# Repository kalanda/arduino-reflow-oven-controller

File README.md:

# Arduino Reflow Oven Controller

This is my custom design of an Arduino Reflow Oven Controller for reflow soldering of SMD components. 

Using a thermocouple to know the temperature inside the oven, this device controls a regular food oven using a SSR(Solid State Relay) for turning the power ON and OFF in order to get the desired temperature on each time to adjust it to the reflow profile. Is possible to choose between leaded and lead-free reflow profiles. The oven was previously modified to take out the thermostat and the timer to make possible to reach higher temperatures. 

The main hardware parts are:

- Arduino Mini
- K type thermocouple
- MAX31855 thermocouple amplifier (breakout from Adafruit) 
- SSR (Solid State Relay) 24-240VAC - 10A 
- LCD Display 16x2
- A couple of buttons and one led
- Some others components like cables, power connectors, power supply, etc...

All the EagleCad files and the Arduino firmware code are available at this repository. 

## Schema

## License

The MIT License (MIT)

Copyright (c) 2015 kalanda

Permission is hereby granted, free of charge, to any person obtaining a copy
of this software and associated documentation files (the "Software"), to deal
in the Software without restriction, including without limitation the rights
to use, copy, modify, merge, publish, distribute, sublicense, and/or sell
copies of the Software, and to permit persons to whom the Software is
furnished to do so, subject to the following conditions:

The above copyright notice and this permission notice shall be included in all
copies or substantial portions of the Software.

THE SOFTWARE IS PROVIDED "AS IS", WITHOUT WARRANTY OF ANY KIND, EXPRESS OR
IMPLIED, INCLUDING BUT NOT LIMITED TO THE WARRANTIES OF MERCHANTABILITY,
FITNESS FOR A PARTICULAR PURPOSE AND NONINFRINGEMENT. IN NO EVENT SHALL THE
AUTHORS OR COPYRIGHT HOLDERS BE LIABLE FOR ANY CLAIM, DAMAGES OR OTHER
LIABILITY, WHETHER IN AN ACTION OF CONTRACT, TORT OR OTHERWISE, ARISING FROM,
OUT OF OR IN CONNECTION WITH THE SOFTWARE OR THE USE OR OTHER DEALINGS IN THE
SOFTWARE.

## Some photos

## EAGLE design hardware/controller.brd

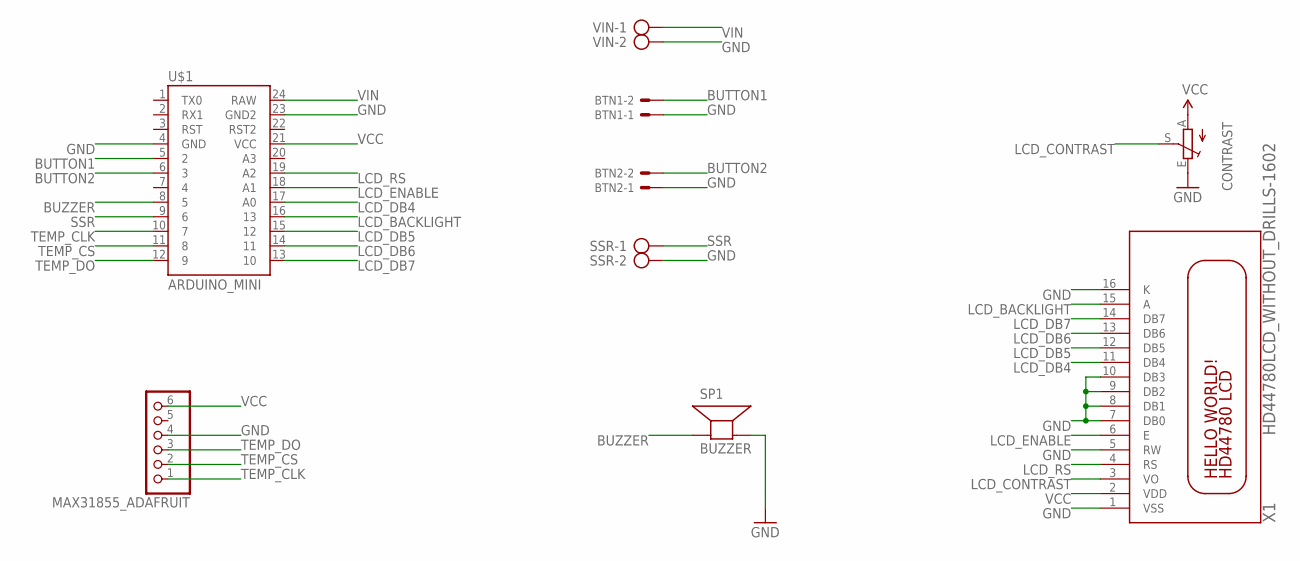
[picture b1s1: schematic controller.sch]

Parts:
BTN1, BTN2: 22-27-2021-02; 6410-02
CONTRAST: TRIM_EU-B25U; B25U
MAX31855_ADAFRUIT: PINHD-1X6; 1X06
SP1: BUZZER; PS12
SSR: AK500/2
U$1: ARDUINO_MINI
VIN: AK500/2
X1: HD44780LCD_WITHOUT_DRILLS-1602; LCD1602

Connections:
BUTTON1: BTN1.2, U$1.5 (2)
BUTTON2: BTN2.2, U$1.6 (3)
BUZZER: SP1.P$1 (+), U$1.8 (5)
GND: BTN1.1, BTN2.1, CONTRAST.E, MAX31855_ADAFRUIT.4, SP1.P$2 (-), SSR.2, U$1.4 (GND), U$1.23 (GND2), VIN.2, X1.1 (VSS), X1.5 (RW), X1.7 (DB0), X1.8 (DB1), X1.9 (DB2), X1.10 (DB3), X1.16 (K)
LCD_BACKLIGHT: U$1.16 (13), X1.15 (A)
LCD_CONTRAST: CONTRAST.S, X1.3 (VO)
LCD_DB4: U$1.17 (A0), X1.11 (DB4)
LCD_DB5: U$1.15 (12), X1.12 (DB5)
LCD_DB6: U$1.14 (11), X1.13 (DB6)
LCD_DB7: U$1.13 (10), X1.14 (DB7)
LCD_ENABLE: U$1.18 (A1), X1.6 (E)
LCD_RS: U$1.19 (A2), X1.4 (RS)
SSR: SSR.1, U$1.9 (6)
TEMP_CLK: MAX31855_ADAFRUIT.1, U$1.10 (7)
TEMP_CS: MAX31855_ADAFRUIT.2, U$1.11 (8)
TEMP_DO: MAX31855_ADAFRUIT.3, U$1.12 (9)
VCC: CONTRAST.A, MAX31855_ADAFRUIT.6, U$1.21 (VCC), X1.2 (VDD)
VIN: U$1.24 (RAW), VIN.1

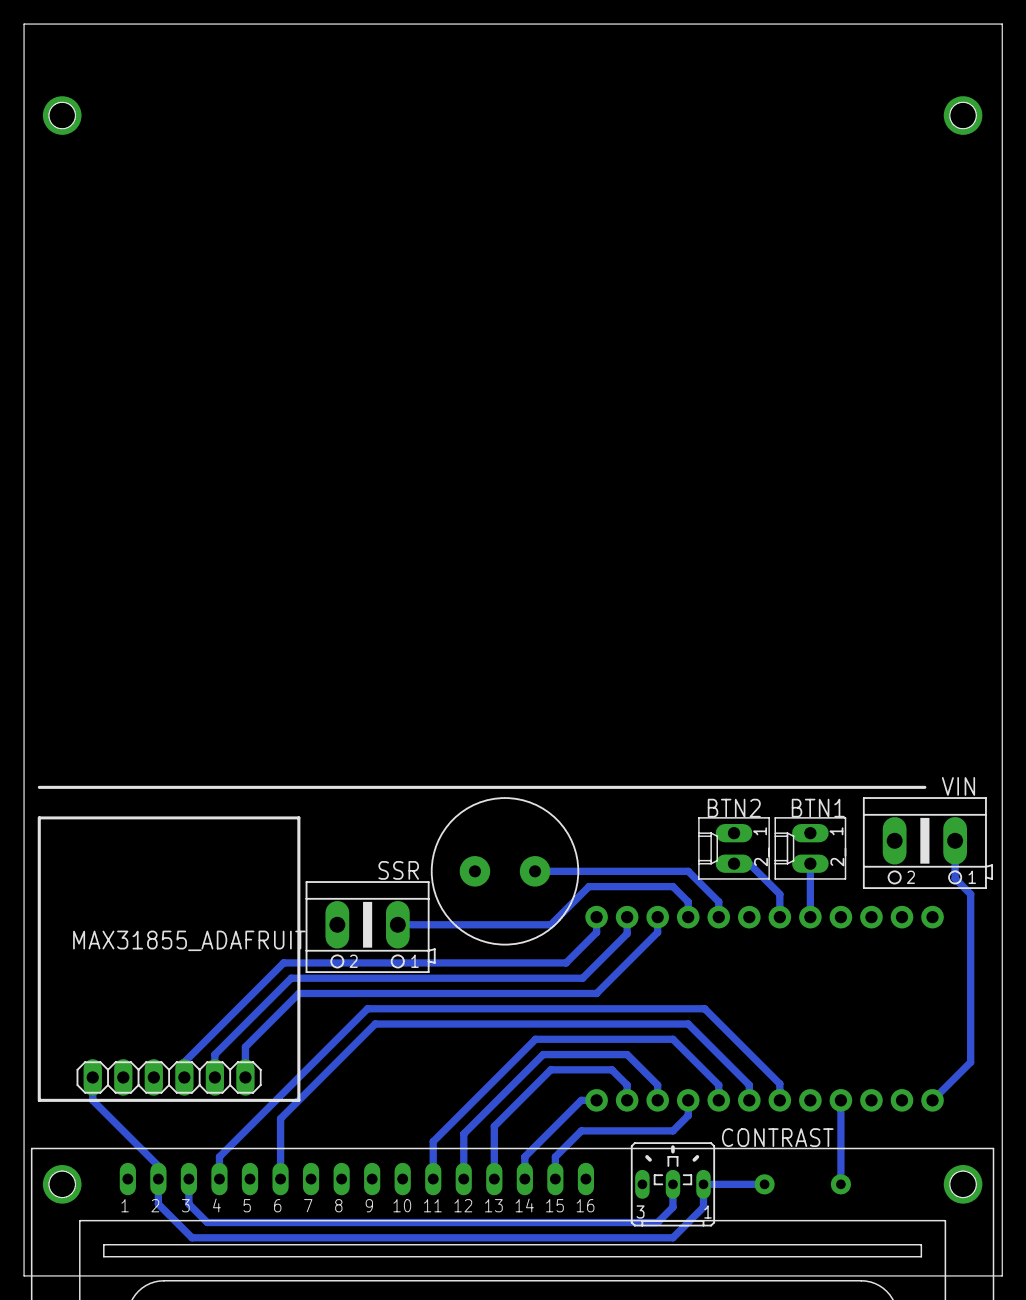
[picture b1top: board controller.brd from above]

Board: 2 copper layers, 81.4 x 104.1 mm, 9 parts (0 on the bottom side), 18 nets.

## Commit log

2015-12-28 Some bugs fixed and lead-free temperature profile added
2017-06-04 Added an special profile for reflow of GPU cards for 10 minutes at 200ºC
2019-12-23 use nokia lcd instead of two line
2019-12-24 code cleanup
2019-12-24 update PID library
    use Arduino library manager
2019-12-24 update thermocouple library
    use arduino library manager
2019-12-24 remap pins for prototype
2019-12-24 use a tone for the buzzer
2019-12-24 store backlight and contrast in EEPROM
2019-12-28 Correct SSR pin
2019-12-29 Fix tones
2019-12-29 start the profile from the current temp
2019-12-29 add PID tuning firmware
2019-12-29 update PID values
2019-12-29 show abort message when exiting monitor
    for consistency
2019-12-31 tune reflow process
2019-12-31 refactor runmodes
    FlexiTimer2 was breaking PWM control of the SSR and had to be refactored out of the applicaiton
2019-12-31 adjust solder profiles
    Add a ramp stage between soak and reflow to allow better control of overall performance.
2019-12-31 add a simulation mode

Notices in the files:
parts and their libraries:
SparkFun-Boards: Licensing: CC v3.0 Share-Alike You are welcome to use this library for commercial purposes.
